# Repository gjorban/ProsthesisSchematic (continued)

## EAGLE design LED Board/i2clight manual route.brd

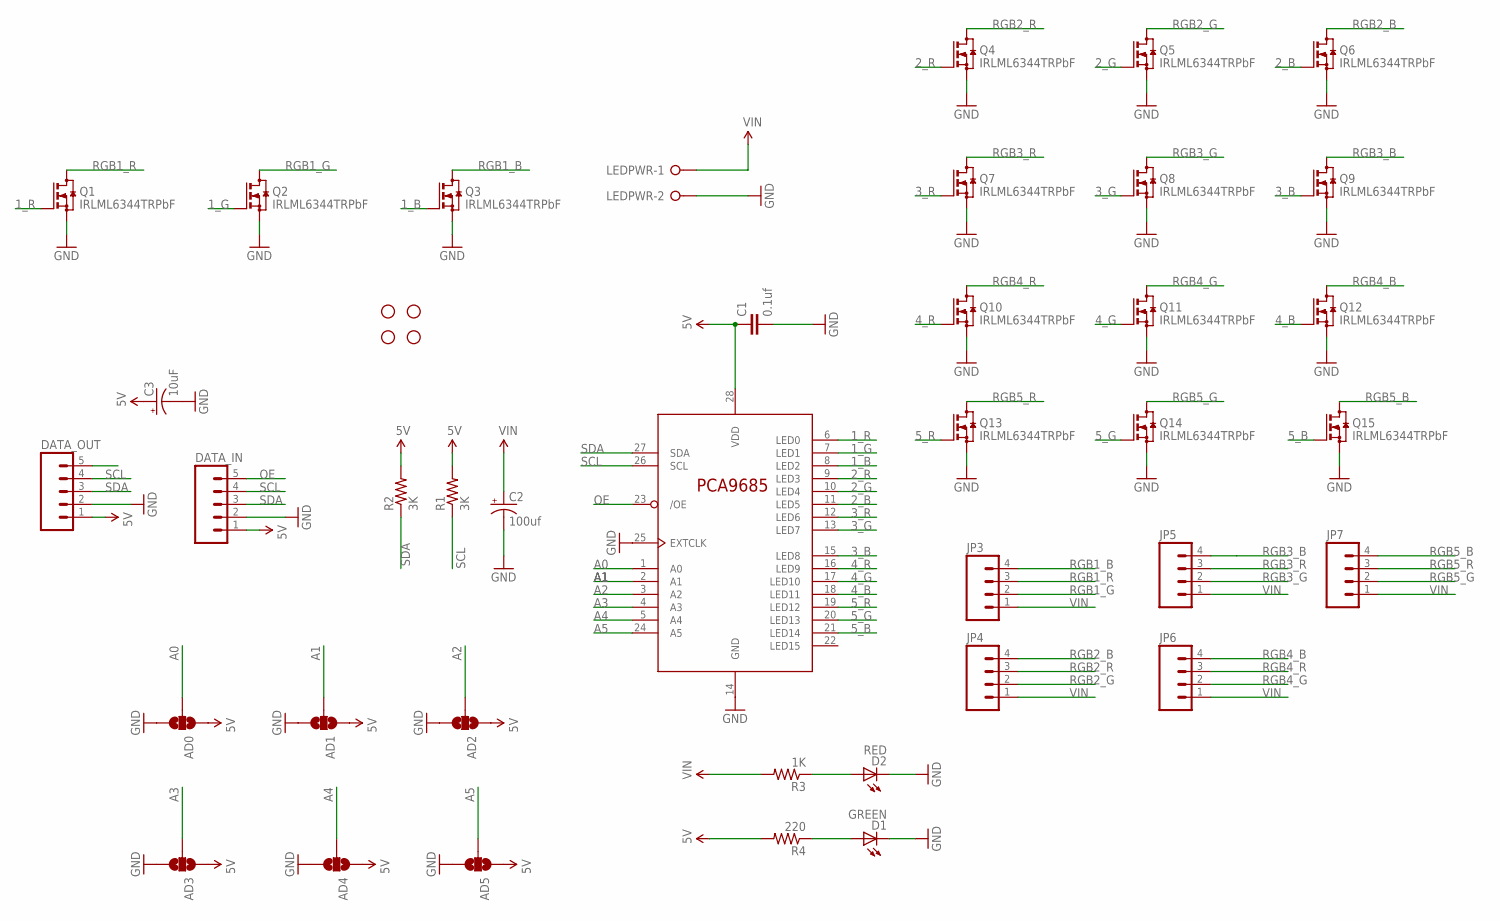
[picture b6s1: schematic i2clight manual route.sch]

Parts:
AD0, AD1, AD2, AD3, AD4, AD5: SOLDERJUMPER_2WAYT; SJ_2
C1: 0.1uf; 0805
C2: 100uf; CPOL-RADIAL-100UF-25V
C3: 10uF; CPOL-RADIAL-10UF-25V
D1: GREEN; LED-1206
D2: RED; LED-1206
DATA_IN: M05PTH_LONGPADS; 1X05_LONGPADS
DATA_OUT: M05PTH_LONGPADS; 1X05_LONGPADS
JP3, JP4, JP5, JP6, JP7: M04POLAR; MOLEX-1X4
LEDPWR: W237-02P; W237-132
PCA9685PW: PCA9685PW; TSSOP28
Q1, Q2, Q3, Q4, Q5, Q6, Q7, Q8, Q9, Q10, Q11, Q12, Q13, Q14, Q15: IRLML6344TRPbF; SOT23
R1, R2: 3K; 0805
R3: 1K; 0805
R4: 220; 0805
STANDOFF1, STANDOFF2, STANDOFF3, STANDOFF4: STAND-OFF

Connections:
1_B: PCA9685PW.8 (LED2), Q3.1 (G)
1_G: PCA9685PW.7 (LED1), Q2.1 (G)
1_R: PCA9685PW.6 (LED0), Q1.1 (G)
2_B: PCA9685PW.11 (LED5), Q6.1 (G)
2_G: PCA9685PW.10 (LED4), Q5.1 (G)
2_R: PCA9685PW.9 (LED3), Q4.1 (G)
3_B: PCA9685PW.15 (LED8), Q9.1 (G)
3_G: PCA9685PW.13 (LED7), Q8.1 (G)
3_R: PCA9685PW.12 (LED6), Q7.1 (G)
4_B: PCA9685PW.18 (LED11), Q12.1 (G)
4_G: PCA9685PW.17 (LED10), Q11.1 (G)
4_R: PCA9685PW.16 (LED9), Q10.1 (G)
5V: AD0.1, AD1.1, AD2.1, AD3.1, AD4.1, AD5.1, C1.1, C3.1 (+), DATA_IN.1, DATA_OUT.1, PCA9685PW.28 (VDD), R1.2, R2.2, R4.2
5_B: PCA9685PW.21 (LED14), Q15.1 (G)
5_G: PCA9685PW.20 (LED13), Q14.1 (G)
5_R: PCA9685PW.19 (LED12), Q13.1 (G)
A0: AD0.2, PCA9685PW.1 (A0)
A1: AD1.2, PCA9685PW.2 (A1)
A2: AD2.2, PCA9685PW.3 (A2)
A3: AD3.2, PCA9685PW.4 (A3)
A4: AD4.2, PCA9685PW.5 (A4)
A5: AD5.2, PCA9685PW.24 (A5)
GND: AD0.3, AD1.3, AD2.3, AD3.3, AD4.3, AD5.3, C1.2, C2.2 (-), C3.2 (-), D1.C, D2.C, DATA_IN.2, DATA_OUT.2, LEDPWR.2, PCA9685PW.14 (GND), PCA9685PW.25 (EXTCLK), Q1.2 (S), Q2.2 (S), Q3.2 (S), Q4.2 (S), Q5.2 (S), Q6.2 (S), Q7.2 (S), Q8.2 (S), Q9.2 (S), Q10.2 (S), Q11.2 (S), Q12.2 (S), Q13.2 (S), Q14.2 (S), Q15.2 (S)
unnamed: D2.A, R3.1
unnamed: D1.A, R4.1
OE: DATA_IN.5, DATA_OUT.5, PCA9685PW.23 (/OE)
RGB1_B: JP3.4, Q3.3 (D)
RGB1_G: JP3.2, Q2.3 (D)
RGB1_R: JP3.3, Q1.3 (D)
RGB2_B: JP4.4, Q6.3 (D)
RGB2_G: JP4.2, Q5.3 (D)
RGB2_R: JP4.3, Q4.3 (D)
RGB3_B: JP5.4, Q9.3 (D)
RGB3_G: JP5.2, Q8.3 (D)
RGB3_R: JP5.3, Q7.3 (D)
RGB4_B: JP6.4, Q12.3 (D)
RGB4_G: JP6.2, Q11.3 (D)
RGB4_R: JP6.3, Q10.3 (D)
RGB5_B: JP7.4, Q15.3 (D)
RGB5_G: JP7.2, Q14.3 (D)
RGB5_R: JP7.3, Q13.3 (D)
SCL: DATA_IN.4, DATA_OUT.4, PCA9685PW.26 (SCL), R1.1
SDA: DATA_IN.3, DATA_OUT.3, PCA9685PW.27 (SDA), R2.1
VIN: C2.1 (+), JP3.1, JP4.1, JP5.1, JP6.1, JP7.1, LEDPWR.1, R3.2

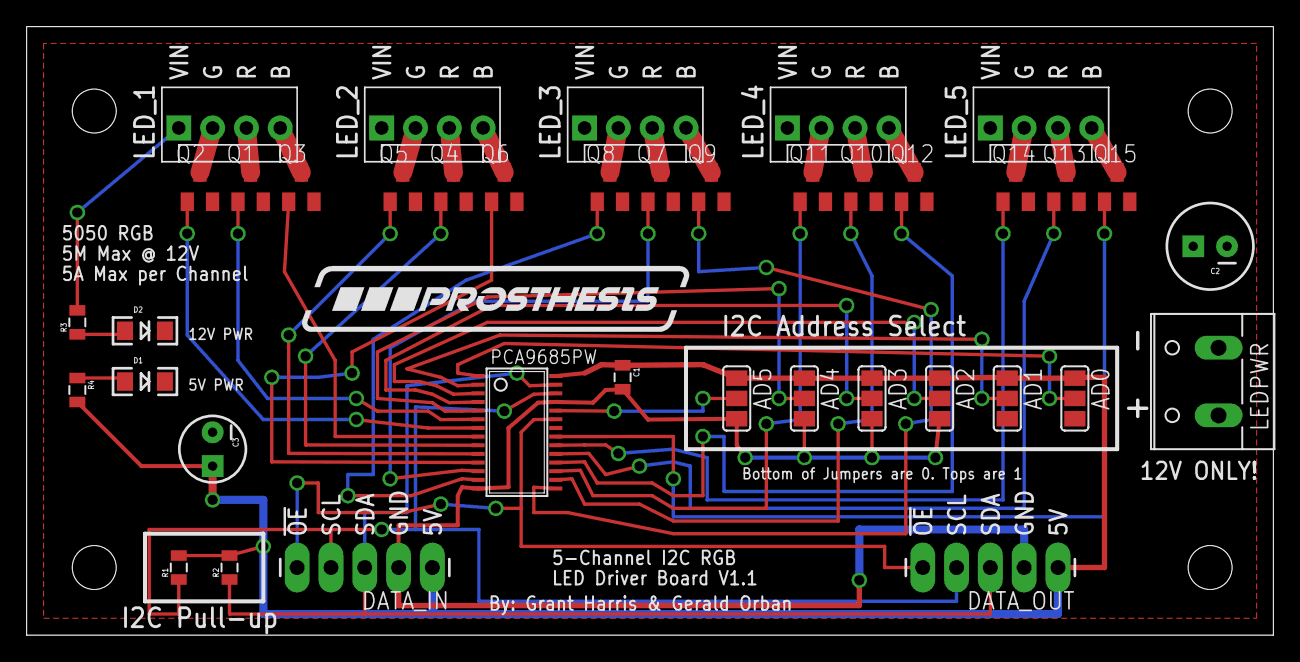
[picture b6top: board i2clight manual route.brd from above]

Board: 2 copper layers, 93.7 x 45.7 mm, 44 parts (0 on the bottom side), 44 nets.

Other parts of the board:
U$2: PROSTHESIS

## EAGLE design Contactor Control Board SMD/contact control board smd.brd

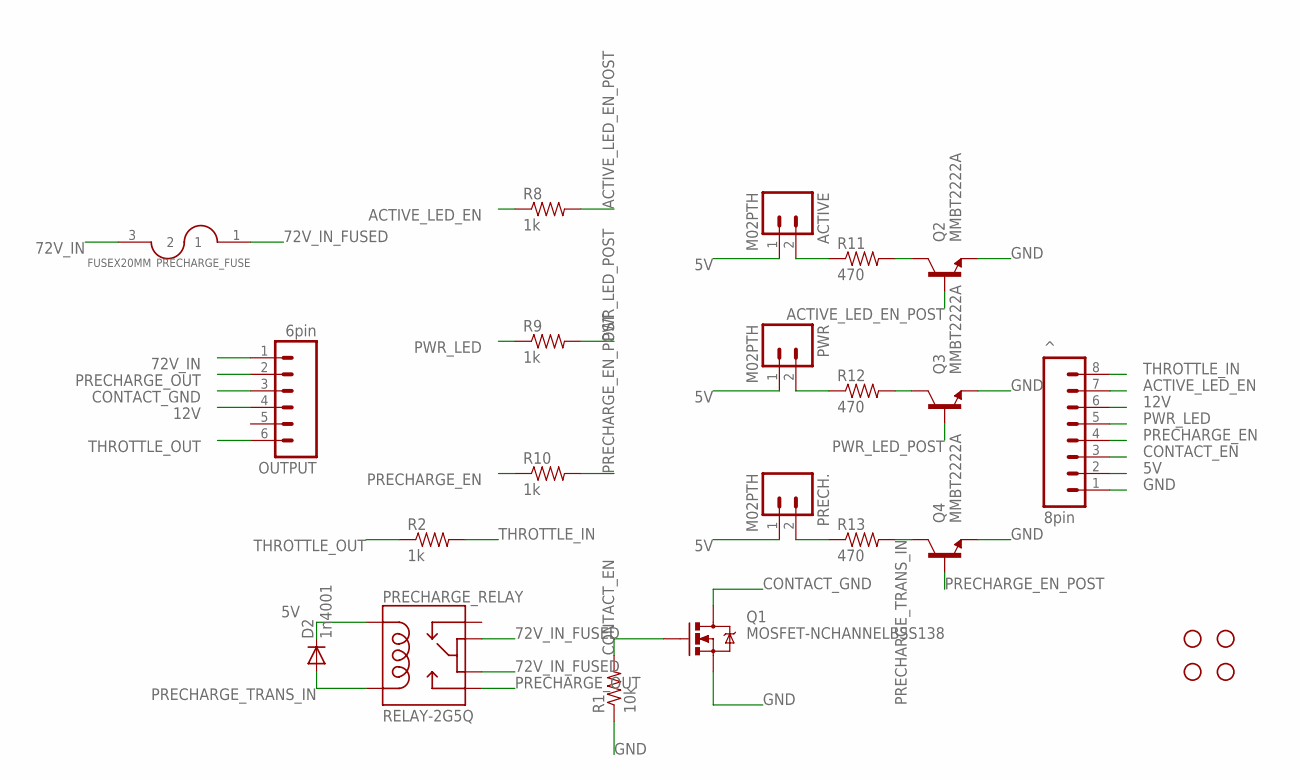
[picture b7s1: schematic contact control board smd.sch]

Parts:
ACTIVE: M02PTH; 1X02
D2: 1n4001; SMA-DIODE
OUTPUT: 6pin; SCREWTERMINAL-3.5MM-6
PRECH.: M02PTH; 1X02
PRECHARGE_FUSE: FUSEX20MM; FUSE_5MM
PRECHARGE_RELAY: RELAY-2G5Q; RELAY-G5V
PWR: M02PTH; 1X02
Q1: MOSFET-NCHANNELBSS138; SOT23
Q2, Q3, Q4: MMBT2222A; SOT23
R1: 10k; 0603-RES
R2, R8, R9, R10: 1k; 0603-RES
R11, R12, R13: 470; 0603-RES
STANDOFF1, STANDOFF2, STANDOFF3, STANDOFF4: STAND-OFF
^: 8pin; 1X08

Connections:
5V: ACTIVE.1, D2.C, PRECH..1, PRECHARGE_RELAY.2, PWR.1, ^.2
12V: OUTPUT.4, ^.6
72V_IN: OUTPUT.1, PRECHARGE_FUSE.3 (2)
72V_IN_FUSED: PRECHARGE_FUSE.1, PRECHARGE_RELAY.5, PRECHARGE_RELAY.6
ACTIVE_LED_EN: R8.1, ^.7
ACTIVE_LED_EN_POST: Q2.1 (B), R8.2
CONTACT_EN: Q1.1 (G), R1.2, ^.3
CONTACT_GND: OUTPUT.3, Q1.3 (D)
GND: Q1.2 (S), Q2.2 (E), Q3.2 (E), Q4.2 (E), R1.1, ^.1
unnamed: Q2.3 (C), R11.2
unnamed: Q3.3 (C), R12.2
unnamed: ACTIVE.2, R11.1
unnamed: PWR.2, R12.1
unnamed: PRECH..2, R13.1
PRECHARGE_EN: R10.1, ^.4
PRECHARGE_EN_POST: Q4.1 (B), R10.2
PRECHARGE_OUT: OUTPUT.2, PRECHARGE_RELAY.10
PRECHARGE_TRANS_IN: D2.A, PRECHARGE_RELAY.9, Q4.3 (C), R13.2
PWR_LED: R9.1, ^.5
PWR_LED_POST: Q3.1 (B), R9.2
THROTTLE_IN: R2.2, ^.8
THROTTLE_OUT: OUTPUT.6, R2.1

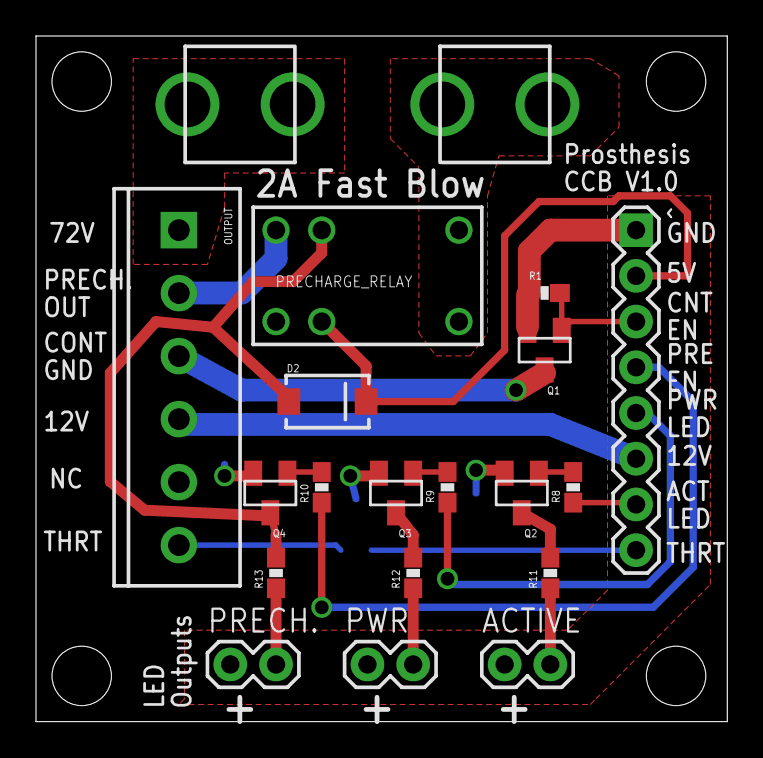
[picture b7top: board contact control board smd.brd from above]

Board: 2 copper layers, 38.4 x 38.1 mm, 24 parts (1 on the bottom side), 22 nets.

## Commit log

2013-07-29 Committing initial schematics
2013-07-30 Adding gitignore for backups and committing WIP files for motor shield.
2013-07-30 Added additional HEX schmitt trigger inverters for debouncing.
    Also fixed pin configurations in the MEGA shield. Some were backards.
    Connected all of the pin headers to their respective components and
    added debouncing for all switch signals.
2013-07-31 Incremental changes for layout.
2013-07-31 Splitting M1 and M2 debouncing signals between the inverters
2013-08-02 Adding capacitor charge state sense for CCB
    Theoretical part selection. Not for usage until testing!
2013-08-02 Added inverter w/ schmitt trigger to the output of the opamp to fixup its outputs.
2013-08-02 Replaced op-amp with voltage comparitor. Need to redo the voltage dividers for a 0-18V range or similar instead of 0-5V
2013-08-02 Updating voltage dividers to common resistor values
2013-08-02 Final draft design for CCB (thru-hole) before proto-boarding.
    Replaced SPST relay with DPDT relay so that its NC connections will
    drain the capacitors and its NO connections will charge them. This way
    we can wait a shorter period of time after powering down the machine
    before servicing!
2013-08-02 Simplified board by removing power LED pin, it's just run from 5V now.
    Swapped pins in the voltage comparator to produce a HIGH output when the
    capacitor voltage drops below the reference voltage (instead of vice
    versa).
2013-08-03 Updating layout to 2"x3". Need to make smaller!
2013-08-04 Redoing voltage dividers so that they produce voltages on the oeprational range of our voltage comparator. Also re-wired the voltage
    monitor for the capacitors to use capacitor voltage and not the voltage
    over the pre-charge resistors.
2013-08-04 Renamed some labels to be more descriptive in their usage.
2013-08-06 Deleting SMD variant of the CCB for now.
    Keeping the two boards in design sync while iterating on one wasn't a
    smart idea. Conversion will happen once the CCB has been validated using
    proto-boards. Did a test route of the CCB using thru-hole parts in a
    2"x3" space and there's a ton of room. Cool!
2013-08-06 Fixing bad note in design
2013-08-08 Added BMS interface board and updated CCB with current limiting resistor
2013-08-09 Updating layout for BMS interface PCB and removed 5V input as it was no longer necessary.
2013-08-13 Opto-coupling precharge signal with op-amp output
2013-08-13 Added buffer to use the output of the Op-Amp and split
    it between an indicator LED and a digital signal output. Tested and
    validated using breadboards
2013-08-14 Using the proper chip package for the buffer chip
2013-08-17 Updated precharge design
    Replaced transistor with a FET as the Arduino can't source enough
    current to trigger both the relay and the LED... At least not with the
    transistors which were specced.
2013-08-18 Mostly routed. Replaced all thru-hole with SMD components. Much smaller!
2013-08-18 Fixed values for FETs and some resistors whcih were cut and paste errors.
2013-08-20 Routed CCB using SMD components. Ready to manufacture!
2013-08-21 Fixed wiring of capacitor charge sensing which caused ground planes to need re-routing
2013-09-08 Finally found part # for fuse holder!
2013-09-08 Routed motor controller arduino shield. Challenging!
2013-09-15 Re-routed motor shield with new molex connectors.
    Still may want to put the CCB headers as a better connector, too. Need
    to source a good 8x2 pin header first. Added prosthesis logo to motor
    board. Added sensor shield schematic (copy of motor board to start)
2013-09-15 Moved MCB titles to places layer from names
    Cleared sensor shield of all components
2013-09-22 CHanged all connectors on MCB to use Molex
    Changed most of the connectors on the BMS interface to use molex as
    well.
2013-09-22 Missed a save before last commit.
2013-09-22 Fixed wire routing on CCB. Added polarity to BMS
    output.
2013-09-23 Moved BMS interface to use an ATX connector.
2013-09-24 Routed BMS interface board and added branding.
    Changed branding for CCB and MCBs
2013-10-08 Added PMS board schematic.
2013-10-12 UPdating resistor packages to sizes which are
    capable of disappating the appropriate amount of power.
2013-10-13 Added capacitors for the three main boards
